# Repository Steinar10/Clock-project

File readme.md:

This is a project I've been working on for a long time, in some of my spare time. The end goal is a wristwatch with RGB leds which act as the hands on an analog watch, with some neat extra features. Now on Github since I recently learned how to git gud(ish).
Firmware in branch test-firmware.

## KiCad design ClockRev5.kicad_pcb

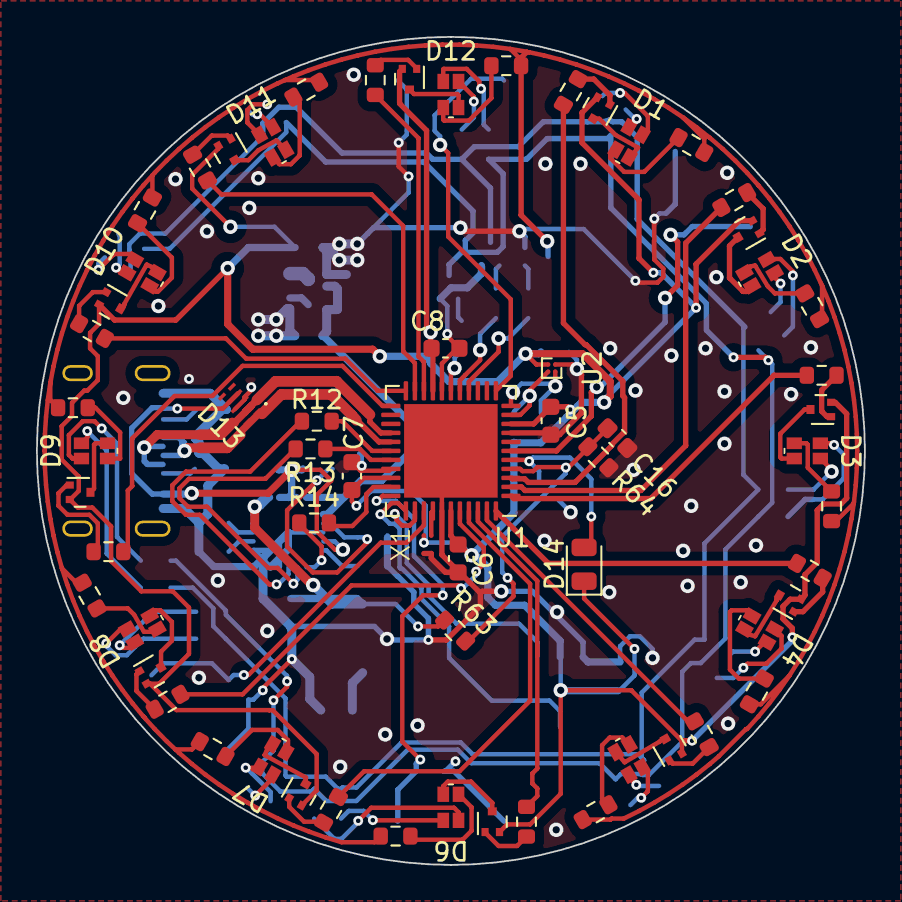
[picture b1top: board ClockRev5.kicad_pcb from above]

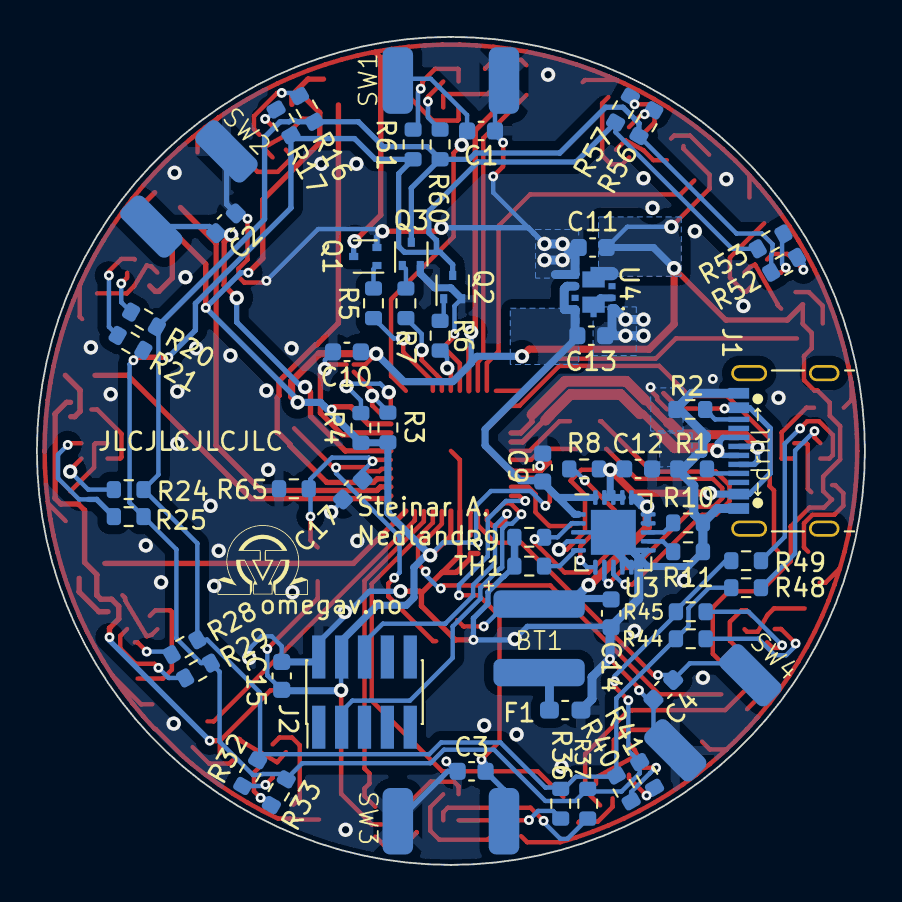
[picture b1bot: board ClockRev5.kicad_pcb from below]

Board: 2 copper layers, 46.0 x 46.0 mm, 125 parts (62 on the bottom side), 113 nets.

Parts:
BT1: 3.7V Li-ion; Battery-wires-solderfootprint
C1, C2, C3, C4, C9, C10, C12, C13, C14: 4.7 uF; C_0603_1608Metric
C5, C6, C7, C8, C16, C17: 100 nF; C_0603_1608Metric
C11, C15: 10 uF; C_0603_1608Metric
D1, D2, D3, D4, D5, D6, D7, D8, D9, D10, D11, D12: LED_0606_LTST-C19HE1WT; LTST-C19HE1WT
D13: PUSB3FR4Z
D14: TEMD6200FX01; D_0805_2012Metric
F1: 500 mA; Fuse_0603_1608Metric_Pad1.05x0.95mm_HandSolder
J1: USB_C_Receptacle_USB2.0; USB_C_Receptacle_Palconn_UTC16-G
J2: Conn_02x05_Odd_Even; PinHeader_2x05_P1.27mm_Vertical_SMD
Q1, Q2, Q3: DMN2710UT-13; SOT-523
Q4, Q5, Q6, Q7, Q8, Q9, Q10, Q11, Q12, Q13, Q14, Q15: SSM3J56MFV; SOT-723
R1, R2, R10: 5.1k; R_0603_1608Metric
R3, R4, R11: 10k; R_0603_1608Metric
R5, R6, R7, R15, R19, R23, R27, R31, R35, R39, R43, R47, R51, R55, R59: 150; R_0603_1608Metric
R8: 270k; R_0603_1608Metric
R9: 110k; R_0603_1608Metric
R12, R13, R14: 1k; R_0603_1608Metric
R16, R20, R24, R28, R32, R36, R40, R44, R48, R52, R56, R60: 10; R_0603_1608Metric
R17, R21, R25, R29, R33, R37, R41, R45, R49, R53, R57, R61: 15; R_0603_1608Metric
R18, R22, R26, R30, R34, R38, R42, R46, R50, R54, R58, R62: 60; R_0603_1608Metric
R63: 680k; R_0603_1608Metric
R64: 2.2M; R_0603_1608Metric
R65: 1.5M; R_0603_1608Metric
SW1, SW2, SW3, SW4: KSS321G LFS; KSS side-actuated switch
TH1: 10k; R_0603_1608Metric
U1: ATxmega64A4U-M; QFN-44-1EP_7x7mm_P0.5mm_EP5.2x5.2mm
U2: MMC5603NJL; WLP-4_0.86x0.86mm_P0.4mm
U3: MCP73871; QFN-20-1EP_4x4mm_P0.5mm_EP2.5x2.5mm
U4: XCL209A333DR
X1: SIT1552AI

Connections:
+BATT: BT1.1 (+), C14.1, R63.1, U3.14 (VBAT), U3.15 (VBAT), U3.16 (Vbat_SENSE)
/Ch1: R15.1, U1.3 (PA7)
/Ch2: R19.1, U1.2 (PA6)
/Ch3: R23.1, U1.1 (PA5)
/Ch4: R27.1, U1.44 (PA4)
/Ch5: R31.1, U1.43 (PA3)
/Ch6: R35.1, U1.42 (PA2)
/Ch7: R39.1, U1.41 (PA1)
/Ch8: R43.1, U1.40 (AREFA/PA0)
/Ch9: R47.1, U1.23 (PD3)
/Ch10: R51.1, U1.22 (PD2)
/Ch11: R55.1, U1.21 (PD1)
/Ch12: R59.1, U1.20 (PD0)
/Ch_B: Q3.3 (D), R16.2, R20.2, R24.2, R28.2, R32.2, R36.2, R40.2, R44.2, R48.2, R52.2, R56.2, R60.2
/Ch_G: Q2.3 (D), R17.2, R21.2, R25.2, R29.2, R33.2, R37.2, R41.2, R45.2, R49.2, R53.2, R57.2, R61.2
/Ch_R: Q1.3 (D), R18.2, R22.2, R26.2, R30.2, R34.2, R38.2, R42.2, R46.2, R50.2, R54.2, R58.2, R62.2
/D+: D13.1 (CH1), D13.10 (N.C._4), J1.A6 (D+), J1.B6 (D+), U1.27 (PD7)
/D-: D13.2 (CH2), D13.9 (N.C._3), J1.A7 (D-), J1.B7 (D-), U1.26 (PD6)
/Gate_B: R7.1, U1.16 (PC6)
/Gate_G: R6.1, U1.17 (PC7)
/Gate_R: R5.1, U1.15 (PC5)
/MCP73871/Vout: C9.1, C13.2, U3.1 (OUT), U3.20 (OUT), U4.6 (CE), U4.8 (VIN)
/Osc: U1.37 (PR1/XTAL1), X1.2 (OUT)
/PDI_CLK: J2.6, U1.35 (~RESET/PDI_CLK)
/PDI_DATA: J2.3, U1.34 (PDI_DATA)
/Photodiode: C17.1, D14.2 (A), R65.1, U1.5 (PB1)
/SCL: R4.2, U1.11 (PC1), U2.A2 (SCL)
/SDA: R3.2, U1.10 (PC0), U2.B2 (SDA)
/STAT1: R12.2, U1.28 (PE0)
/STAT2: R13.2, U1.29 (PE1)
/SW1: C1.1, SW1.2, U1.12 (PC2)
/SW2: C2.1, SW2.2, U1.6 (PB2)
/SW3: C3.1, SW3.2, U1.33 (PE3)
/SW4: C4.1, SW4.2, U1.36 (PR0/XTAL2)
/~PG: R14.2, U1.32 (PE2)
GND: C1.2, C2.2, C3.2, C4.2, C5.1, C6.1, C7.1, C8.1, C9.2, C10.1, C11.1, C12.1, C13.1, C14.2, C15.2, C16.2, C17.2, D13.3 (GND_1), D13.8 (GND_2), F1.1, J1.A1 (GND), J1.A12 (GND), J1.B1 (GND), J1.B12 (GND), J2.2, Q1.2 (S), Q2.2 (S), Q3.2 (S), R1.1, R2.1, R9.1, R10.1, R11.1, R64.2, R65.2, SW1.1, SW2.1, SW3.1, SW4.1, TH1.2, U1.8 (GND), U1.18 (GND), U1.30 (GND), U1.38 (GND), U1.45 (GND), U2.A1 (VSA), U3.3 (SEL), U3.9 (~TE), U3.10 (VSS), U3.11 (VSS), U3.21 (VSS), U4.1 (PVSS), U4.5 (AVSS), X1.1 (GND), X1.4 (GND)
unnamed: BT1.2 (-), F1.2
unnamed: D1.3 (A), Q4.3 (D)
unnamed: D1.2 (BK), R16.1
unnamed: D1.1 (GK), R17.1
unnamed: D1.4 (RK), R18.1
unnamed: D2.3 (A), Q5.3 (D)
unnamed: D2.2 (BK), R20.1
unnamed: D2.1 (GK), R21.1
unnamed: D2.4 (RK), R22.1
unnamed: D3.3 (A), Q6.3 (D)
unnamed: D3.2 (BK), R24.1
unnamed: D3.1 (GK), R25.1
unnamed: D3.4 (RK), R26.1
unnamed: D4.3 (A), Q7.3 (D)
unnamed: D4.2 (BK), R28.1
unnamed: D4.1 (GK), R29.1
unnamed: D4.4 (RK), R30.1
unnamed: D5.3 (A), Q8.3 (D)
unnamed: D5.2 (BK), R32.1
unnamed: D5.1 (GK), R33.1
unnamed: D5.4 (RK), R34.1
unnamed: D6.3 (A), Q9.3 (D)
unnamed: D6.2 (BK), R36.1
unnamed: D6.1 (GK), R37.1
unnamed: D6.4 (RK), R38.1
unnamed: D7.3 (A), Q10.3 (D)
unnamed: D7.2 (BK), R40.1
unnamed: D7.1 (GK), R41.1
unnamed: D7.4 (RK), R42.1
unnamed: D8.3 (A), Q11.3 (D)
unnamed: D8.2 (BK), R44.1
unnamed: D8.1 (GK), R45.1
unnamed: D8.4 (RK), R46.1
unnamed: D9.3 (A), Q12.3 (D)
unnamed: D9.2 (BK), R48.1
unnamed: D9.1 (GK), R49.1
unnamed: D9.4 (RK), R50.1
unnamed: D10.3 (A), Q13.3 (D)
unnamed: D10.2 (BK), R52.1
unnamed: D10.1 (GK), R53.1
unnamed: D10.4 (RK), R54.1
unnamed: D11.3 (A), Q14.3 (D)
unnamed: D11.2 (BK), R56.1
unnamed: D11.1 (GK), R57.1
unnamed: D11.4 (RK), R58.1
unnamed: D12.3 (A), Q15.3 (D)
unnamed: D12.2 (BK), R60.1
unnamed: D12.1 (GK), R61.1
unnamed: D12.4 (RK), R62.1
unnamed: J1.A5 (CC1), R1.2
unnamed: J1.B5 (CC2), R2.2
unnamed: Q1.1 (G), R5.2
unnamed: Q2.1 (G), R6.2
unnamed: Q3.1 (G), R7.2
unnamed: Q4.1 (G), R15.2
unnamed: Q5.1 (G), R19.2
unnamed: Q6.1 (G), R23.2
unnamed: Q7.1 (G), R27.2
unnamed: Q8.1 (G), R31.2
unnamed: Q9.1 (G), R35.2
unnamed: Q10.1 (G), R39.2
unnamed: Q11.1 (G), R43.2
unnamed: Q12.1 (G), R47.2
unnamed: Q13.1 (G), R51.2
unnamed: Q14.1 (G), R55.2
unnamed: Q15.1 (G), R59.2
unnamed: C16.1, R63.2, R64.1, U1.4 (AREFB/PB0)
unnamed: R10.2, U3.13 (PROG1)
unnamed: R11.2, U3.12 (PROG3)
unnamed: R12.1, U3.8 (STAT1/~LBO)
unnamed: R13.1, U3.7 (STAT2)
unnamed: TH1.1, U3.5 (THERM)
unnamed: R8.1, R9.2, U3.2 (VPCC)
unnamed: R14.1, U3.6 (~PG)
unnamed: U4.2 (LX), U4.9 (L1_1), U4.11 (L1_2)
VBUS: C12.2, D13.4 (CH3), D13.7 (N.C._2), J1.A4 (VBUS), J1.A9 (VBUS), J1.B4 (VBUS), J1.B9 (VBUS), R8.2, U3.4 (PROG2), U3.17 (CE), U3.18 (IN), U3.19 (IN)
VCC: C5.2, C6.2, C7.2, C8.2, C10.2, C11.2, C15.1, D14.1 (K), J2.4, Q4.2 (S), Q5.2 (S), Q6.2 (S), Q7.2 (S), Q8.2 (S), Q9.2 (S), Q10.2 (S), Q11.2 (S), Q12.2 (S), Q13.2 (S), Q14.2 (S), Q15.2 (S), R3.1, R4.1, U1.9 (VCC), U1.19 (VCC), U1.31 (VCC), U1.39 (AVCC), U2.B1 (VDD), U4.4 (VOUT), U4.10 (L2_1), U4.12 (L2_2), X1.3 (Vdd)

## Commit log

2023-11-14 Added project to Git.
2023-12-16 New branch with firmware, woohoo! Currently testing fancy ways of getting arbitrary LED colours with as low power consumption as possible :)
2023-12-17 Inverted all pins controlling the high-side PMOSes, and updated (hopefully all) functions using those pins. Tried using MPCMASK for this, need to test this soon. Commented out some functions I think 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
2023-12-17 Update readme.md
    Small spelling correction, updated firmware status.
2023-12-20 Fixed a bug where the CCA interrupt would look outside the arrays and turn on stupid pins. MPCMASK tested, works well :)
2023-12-22 Changed colours array structure. Moved main loop to periodic TCC1 interrupt. Made a basic fading colour cycle LED.
2023-12-22 Fixed bug where setColor would let you write to 255 in the colour array and not to 11.
2023-12-23 Organized the code better.
2024-01-17 Added/improved comments, structured some things a little better, fixed(?) colour cycle
